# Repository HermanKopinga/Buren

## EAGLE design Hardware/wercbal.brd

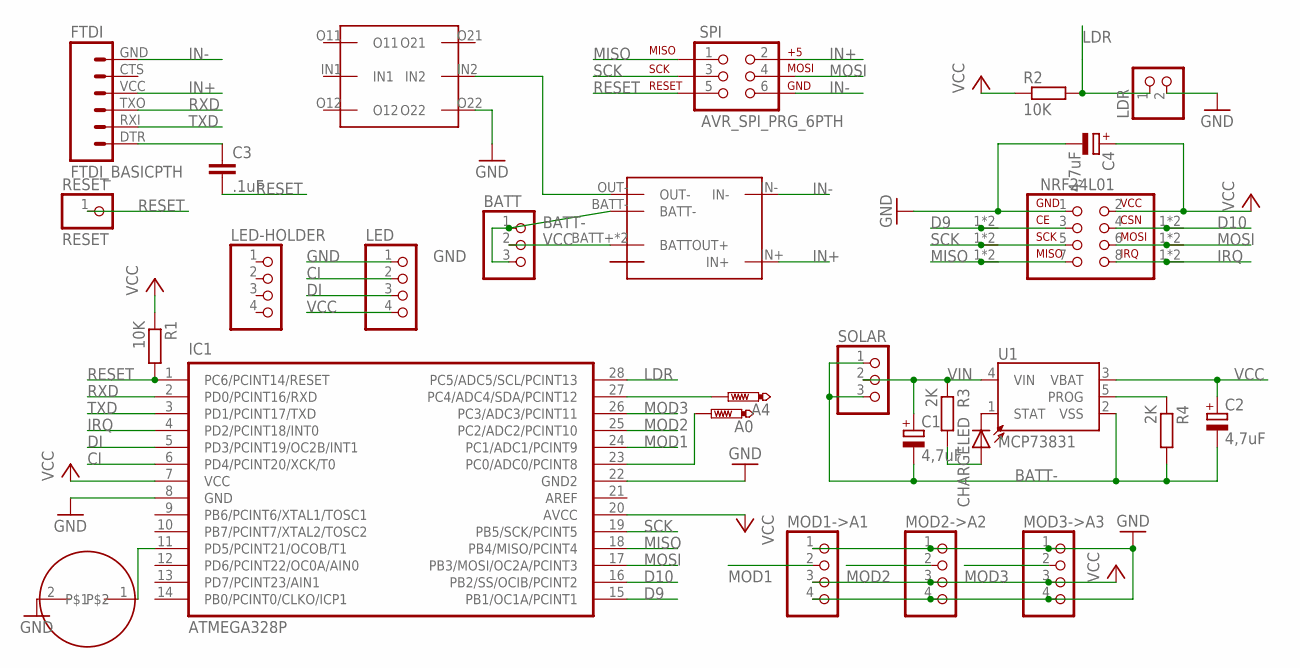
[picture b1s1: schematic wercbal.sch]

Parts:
A0, A4: PTR1PAD1-13; P1-13
BATT: PINHD-1X3; 1X03
C1, C2, C4: 4,7uF; E2-5
C3: .1uF; C025-024X044
CHARGELED: LED5MM
FTDI: FTDI_BASICPTH; FTDI_BASIC
IC1: ATMEGA328P; DIL28-N
LDR: PINHD-1X2; 1X02
LED: GND; 1X04
LED-HOLDER: PINHD-1X4; 1X04
MOD1->A1, MOD2->A2, MOD3->A3: PINHD-1X4; 1X04
NRF24L01: NRF24L01+
R1, R2: 10K; 0204/5
R3, R4: 2K; 0207/7
RESET: RESET; 1X01
SCHAKELAAR: MINIDPDTANGLE; MINIDPDT-ANGLE
SOLAR: PINHD-1X3; 1X03
SPI: AVR_SPI_PRG_6PTH; 2X3
U1: MCP73831; SOT23-5
U$1: TP4056
U$2: PIEZO14MM; PIEZO
U$3, U$4, U$5, U$6, U$7, U$8: BREAKAWAY; BREAK-AWAY

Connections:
A0: A0.TP, IC1.23 (PC0/ADC0/PCINT8)
BATT-: BATT.1, BATT.3, C1.-, C2.-, R4.2, SOLAR.1, SOLAR.3, U1.2 (VSS), U$1.BATT-
CI: IC1.6 (PD4/PCINT20/XCK/T0), LED.2
D9: IC1.15 (PB1/OC1A/PCINT1), NRF24L01.3, U$3.1, U$3.2
D10: IC1.16 (PB2/SS/OCIB/PCINT2), NRF24L01.4, U$6.1, U$6.2
DI: IC1.5 (PD3/PCINT19/OC2B/INT1), LED.3
GND: C4.-, IC1.8 (GND), IC1.22 (GND2), LDR.2, LED.1, MOD1->A1.1, MOD1->A1.4, MOD2->A2.1, MOD2->A2.4, MOD3->A3.1, MOD3->A3.4, NRF24L01.1, SCHAKELAAR.O22, U$2.2
IN+: FTDI.VCC (4), SPI.2, U$1.IN+
IN-: FTDI.GND (6), SPI.6, U$1.IN-
IRQ: IC1.4 (PD2/PCINT18/INT0), NRF24L01.8, U$8.1, U$8.2
LDR: IC1.28 (PC5/ADC5/SCL/PCINT13), LDR.1, R2.2
MISO: IC1.18 (PB4/MISO/PCINT4), NRF24L01.7, SPI.1, U$5.1, U$5.2
MOD1: IC1.24 (PC1/ADC1/PCINT9), MOD1->A1.2
MOD2: IC1.25 (PC2/ADC2/PCINT10), MOD2->A2.2
MOD3: IC1.26 (PC3/ADC3/PCINT11), MOD3->A3.2
MOSI: IC1.17 (PB3/MOSI/OC2A/PCINT3), NRF24L01.6, SPI.4, U$7.1, U$7.2
unnamed: CHARGELED.K (C), U1.1 (STAT)
unnamed: CHARGELED.A, R3.2
unnamed: SCHAKELAAR.IN2, U$1.OUT-
unnamed: IC1.11 (PD5/PCINT21/OCOB/T1), U$2.1
unnamed: C3.1, FTDI.DTR (1)
unnamed: A4.TP, IC1.27 (PC4/ADC4/SDA/PCINT12)
PROG: R4.1, U1.5 (PROG)
RESET: C3.2, IC1.1 (PC6/PCINT14/RESET), R1.2, RESET.1, SPI.5
RXD: FTDI.TXO (3), IC1.2 (PD0/PCINT16/RXD)
SCK: IC1.19 (PB5/SCK/PCINT5), NRF24L01.5, SPI.3, U$4.1, U$4.2
TXD: FTDI.RXI (2), IC1.3 (PD1/PCINT17/TXD)
VCC: BATT.2, C2.+, C4.+, IC1.7 (VCC), IC1.20 (AVCC), LED.4, MOD1->A1.3, MOD2->A2.3, MOD3->A3.3, NRF24L01.2, R1.1, R2.1, U1.3 (VBAT), U$1.BATT+ (BATTOUT+), U$1.OUT+ (BATTOUT+)
VIN: C1.+, R3.1, SOLAR.2, U1.4 (VIN)

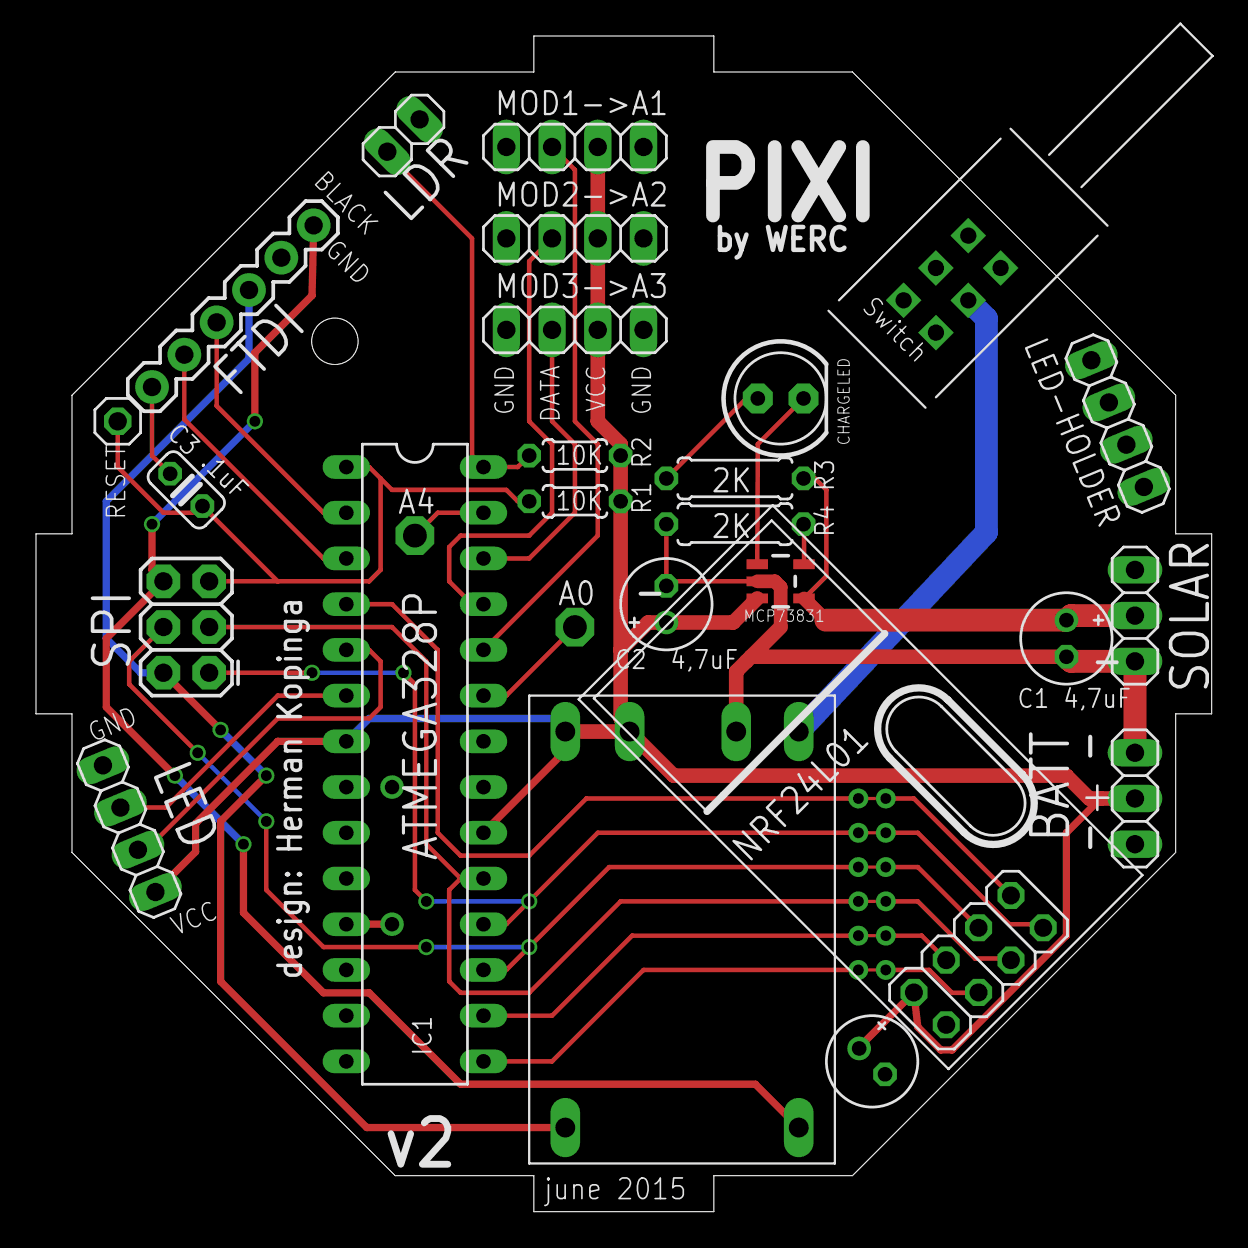
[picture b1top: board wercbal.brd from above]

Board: 2 copper layers, 65.3 x 65.3 mm, 34 parts (0 on the bottom side), 29 nets.

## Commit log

2015-06-19 Initial commit
    Based on cobbled together internet examples.
2015-06-19 for spicing up the code
2015-07-08 starting point, Message construction, color change
2015-07-08 Added hardware files
    Eagle files & PDF for convenience.
2015-07-09 added speaker, + protocol documentation
2015-07-09 New packet layout & beautification.
    /*
    1 time (2 bytes) start time for color (fraction: 8 bits.8 bits
    0-255.0-255)
    2 Frequency (byte) freq for color calcualtion / 100
    3 Broad (byte) color calculation
    4 Center (byte) range of color calculation
2015-07-09 Type conversion corrections for protocol. Added cricket.
2015-07-09 Adding time based color change
2015-07-09 added button pin for send
2015-07-09 Activated cricket, sane defaults for sending & code beautification
2015-07-09 cricket was a variable and a function, whoops
2015-07-09 added intensity value to button press
2015-07-09 Added color shift variable to button
2015-07-09 More extreme colorshift & better rest.
2015-07-09 turn off led
2015-07-09 Undo colorShift fuckup (we are learning github)
2015-07-09 Delay sanitation. 3 led-periods deaf.
2015-07-09 Brute force Olav experiment.
2015-07-10 Added ledTime to the protocol, time LED is on.
2015-07-10 Damn you semicolon.
2015-07-10 updated, color, fade over multiple pixies, battery level chek, make color
2015-07-10 Major code resturcture, better comments, documenting header & bootloader.
2015-07-10 less machine dependent.
2015-07-10 Whoops, lost the defaults for the origin PIXI.
2015-07-10 Added default value on button press: fadeOut
2015-07-11 Attempt at fixing the intensity chek so a signal dies after x amountt of pixis
    byte rolls over
    Casting the intensity byte to an int and back.
    looks almost there but not really :)
2015-07-14 Fixed the intensity rollover (thanx Demi)
2015-07-14 rough fade functions for Olav's benefit :)
2015-07-14 fade code added but not in loop yet, thanks Demi! More tomorrow.
    not in loop yet since we are still doing blocking delays :(
2015-07-14 actually removed from loop, was bogus :-S
    Mooooore booooooze!
2015-07-16 Added Sleep and Gamma, all untested.
2015-07-16 loop() is now non-blocking (not tested)
2015-07-16 Sleep debugging -> we've got action. Fading is broken.
2015-07-16 Fix the fixing fixers
2015-07-16 And now, David
2015-07-16 day 1
2015-07-17 Buren senders, color dominance
2016-03-01 sleep and wakeup
    - Fixt sleep, and wakeup,
    - bat status on boot
    - close eyes before sleeping
